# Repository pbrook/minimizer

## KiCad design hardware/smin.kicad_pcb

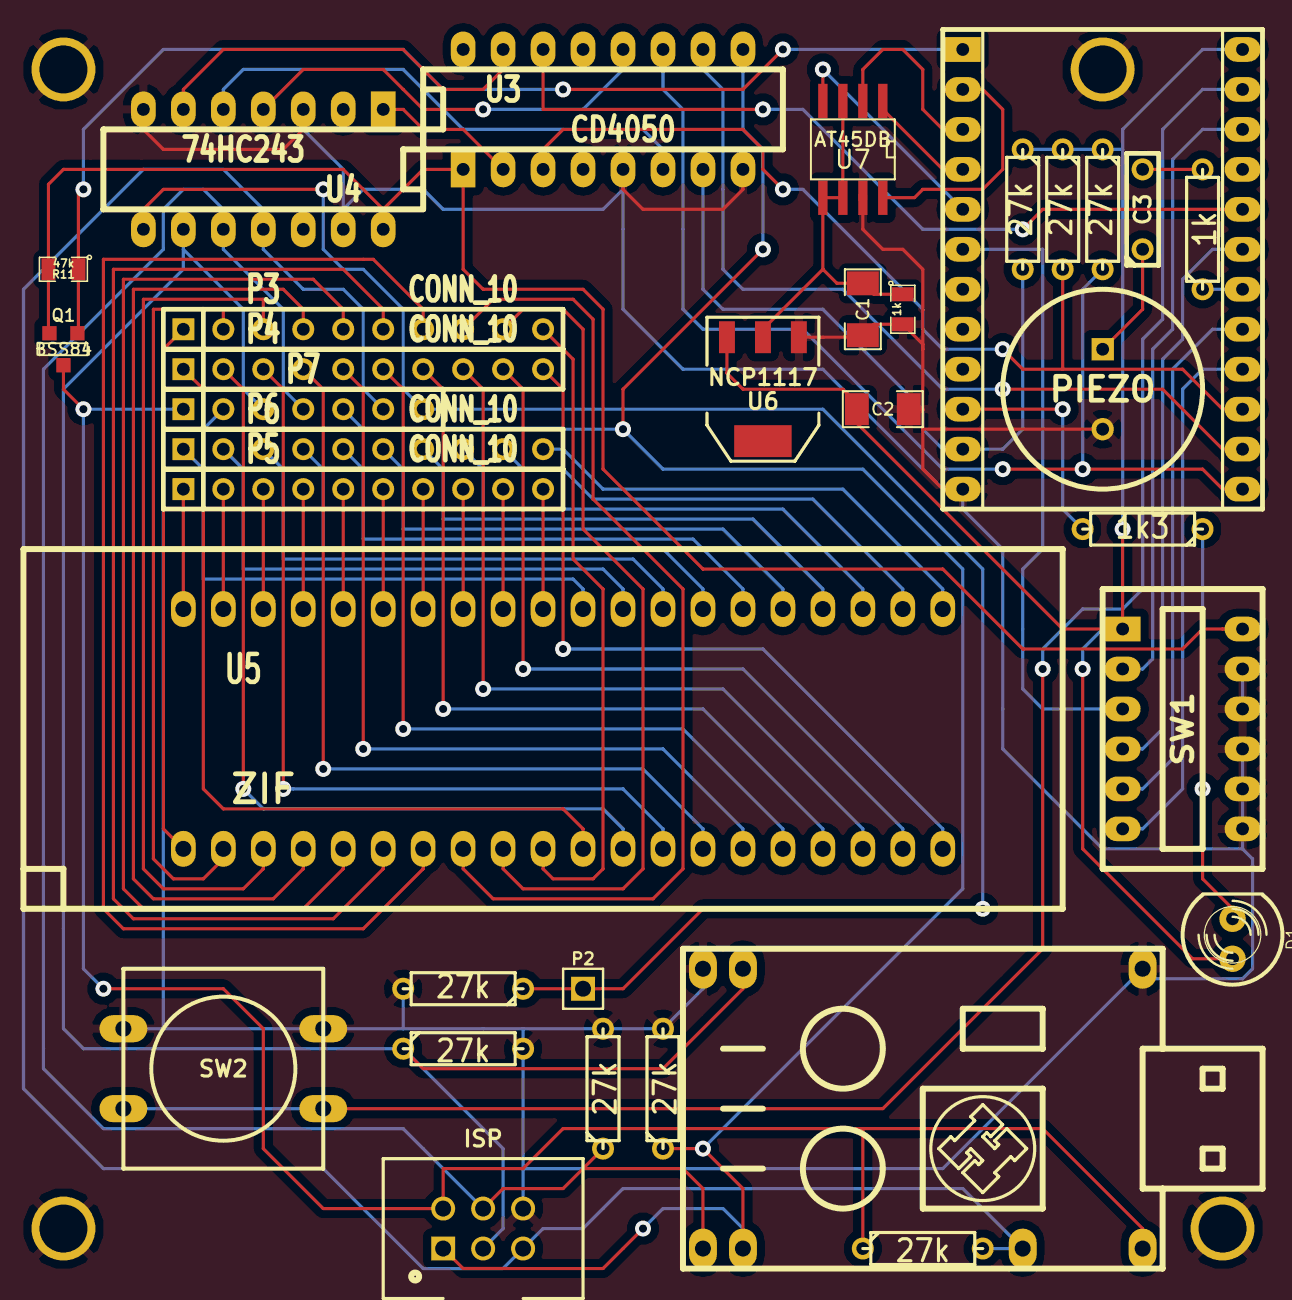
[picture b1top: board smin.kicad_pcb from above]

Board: 2 copper layers, 46 parts (1 on the bottom side), 75 nets.

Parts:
C1, C2: 10u; SM1206
C3: 100n; C2
D1: LED; LED-5MM
HACKSPACE_LOGO: VAL**; HACKSPACE_LOGO
LOGO_SMALL: VAL**; LOGO_SMALL
P1: ISP; AVRISP6
P2: CONN_1; PIN_ARRAY_1
P3, P4, P5, P6: CONN_10; SIL-10
P7: CONN_7; SIL-7
P8, P9, P10, P11: CONN_1; HOLE3
Q1: BSS84; SOT23GDS
R1, R2, R3, R5, R6, R7, R8, R9: 27k; R3
R4: 1k; R3
R10: 1k3; R3
R11: 47k; SM0805
R12: 1k; SM0805
SW1: SW_DIP_6; SWDIP6
SW2: SW_PUSH; SW_PUSH-12
TP1, TP10, TP11, TP12, TP13, TP21, TP24: CONN_1; POGO
U1: MINIMUS
U3: CD4050; DIP-16__300_ELL
U4: 74HC243; DIP-14__300_ELL
U5: ZIF; ZIF40-600
U6: NCP1117; SOT223
U7: AT45DB; SO8-2
X1: PIEZO; BUZ3-5

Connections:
+3.3V: C1.1, R12.1, U6.2, U7.3, U7.5, U7.6
+5V: C2.1, D1.1, R1.1, R2.1, R3.1, SW1.1, U1.24, U6.3
/CFG1: SW2.1, U1.23
/CFG2: SW1.2, U1.22
/CFG3: SW1.3, U1.6
/CFG4: SW1.4, U1.19
/CFG5: SW1.5, U1.17
/CFG6: SW1.6, U1.16
/VCC: Q1.S, R11.2, SW1.12, U3.1, U4.14
GND: C1.2, C2.2, P1.6, P7.2, P8.1, P9.1, P10.1, P11.1, R6.2, R7.2, R8.2, R9.2, R12.2, SW1.7, SW1.8, SW1.9, SW1.10, SW1.11, SW2.2, TP1.1, TP11.1, U1.12, U3.5, U3.8, U4.3, U4.7, U4.13, U6.1, U7.7, X1.2
MISO: P1.1, P7.5, R8.1, TP13.1, U3.9
MOSI: P1.4, P7.4, R6.1, TP12.1, U4.10
unnamed: U3.15, U4.6
unnamed: D1.2, R10.1
unnamed: R10.2, U1.10
unnamed: U1.4, U7.1
unnamed: U3.6, U4.5
unnamed: U1.5, U7.4
unnamed: U1.2, U7.8
unnamed: U1.14, U3.10
unnamed: Q1.G, R11.1, U1.1
unnamed: U1.3, U7.2
unnamed: P5.5, U5.36
unnamed: P6.3, U5.28
unnamed: P6.2, U5.29
unnamed: P6.1, U5.30
unnamed: P5.10, U5.31
unnamed: P5.9, U5.32
unnamed: P5.8, U5.33
unnamed: P5.7, U5.34
unnamed: P5.6, U5.35
unnamed: P6.4, U5.27
unnamed: P5.4, U5.37
unnamed: P5.3, U5.38
unnamed: P5.2, U5.39
unnamed: P5.1, U5.40
unnamed: P6.5, U5.26
unnamed: P6.6, U5.25
unnamed: P6.7, U5.24
unnamed: P6.8, U5.23
unnamed: P6.9, U5.22
unnamed: P6.10, U5.21
unnamed: P4.10, U5.20
unnamed: P4.9, U5.19
unnamed: P4.8, U5.18
unnamed: P4.7, U5.17
unnamed: P4.6, U5.16
unnamed: P4.5, U5.15
unnamed: P4.3, U5.13
unnamed: P4.4, U5.14
unnamed: P4.2, U5.12
unnamed: C3.2, R4.2
unnamed: P4.1, U5.11
unnamed: R2.2, U1.13, U3.11
unnamed: U1.20, U3.14
unnamed: P3.3, U5.3
unnamed: P3.1, U5.1
unnamed: P3.2, U5.2
unnamed: P3.4, U5.4
unnamed: P3.5, U5.5
unnamed: P3.6, U5.6
unnamed: P3.7, U5.7
unnamed: P3.8, U5.8
unnamed: P3.9, U5.9
unnamed: P3.10, U5.10
unnamed: U3.2, U4.1
unnamed: R3.2, U1.11, U3.7
unnamed: U3.12, U4.4
unnamed: C3.1, X1.1
unnamed: R4.1, U1.18
unnamed: R1.2, U1.15, U3.3
RST: P1.5, P7.6, R5.2, TP21.1, U4.11
SCK: P1.3, P7.3, R7.1, TP10.1, U4.9
Vt: P1.2, P7.1, Q1.D, R5.1, TP24.1
XCK: P2.1, P7.7, R9.1, U4.8

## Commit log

2013-09-11 Initial hardware design
2013-09-11 Import from LUFA-130901
    Import AVRISP-MKII sources from LUFA-130901
2013-09-11 Add firmware .gitignore
    Import .gitignore from LUFA
2013-09-11 Build for minimus
    Build for minimus by default.
2013-09-11 Embedded mnimius programmer
    Add embedded minimus programming code.
2013-09-11 Audio support.
2013-09-23 Move descriptor to flash
    Put AVRISP_ConfigurationDescriptor in flash when possible.
2013-10-11 Initial mass storage code.
    Mass storage support.
2013-10-24 More minimizer code
    Fix stack overflow in ISP code.
    Add initial minimizer code.
    Remove old minimus hack.
2013-10-24 Power control
    Implement target power control.
2013-10-25 Fix standalone flasher
    Make standalone flasher work.
2013-10-25 Reduce memory use
    Reduce FATFS buffer to half a sector.
2013-10-25 USB mode power
    Disable target power when in USB mass storage mode.
2013-10-25 Enable LFN
    Enable long file names.
2013-10-25 Fix FAT lookup
    Fix FAT offset calculations.
2013-10-25 SREC start address
    Handle type 3 (start address) S-Records.
2013-10-25 Revert code page
    Revert back to old code page due to memory use.
2013-10-25 Fuse programming tweaks
    Delay after programming fuse. Check if value was programmed correctly.
2013-10-25 Remove superfluous delays
    Remove delays from debugging.
2013-11-06 Better USB ID
    Use Atmel mass storage device ID
2013-11-06 Make button work
    Make external button work
    Blink after flashing for longer.
2013-12-03 Add bulk mode
    Bulk programming mode (no delay) via DIP3.
2013-12-14 PCB fixes
2013-12-14 First pass at rev2 hardware
2013-12-15 USB eject
    Implement SCSI START STOP UNIT command. Allows eject/safe removal
    When in mass storage mode.

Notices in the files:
hardware/smin.kicad_pcb:
(C) 2013 Paul Brook
